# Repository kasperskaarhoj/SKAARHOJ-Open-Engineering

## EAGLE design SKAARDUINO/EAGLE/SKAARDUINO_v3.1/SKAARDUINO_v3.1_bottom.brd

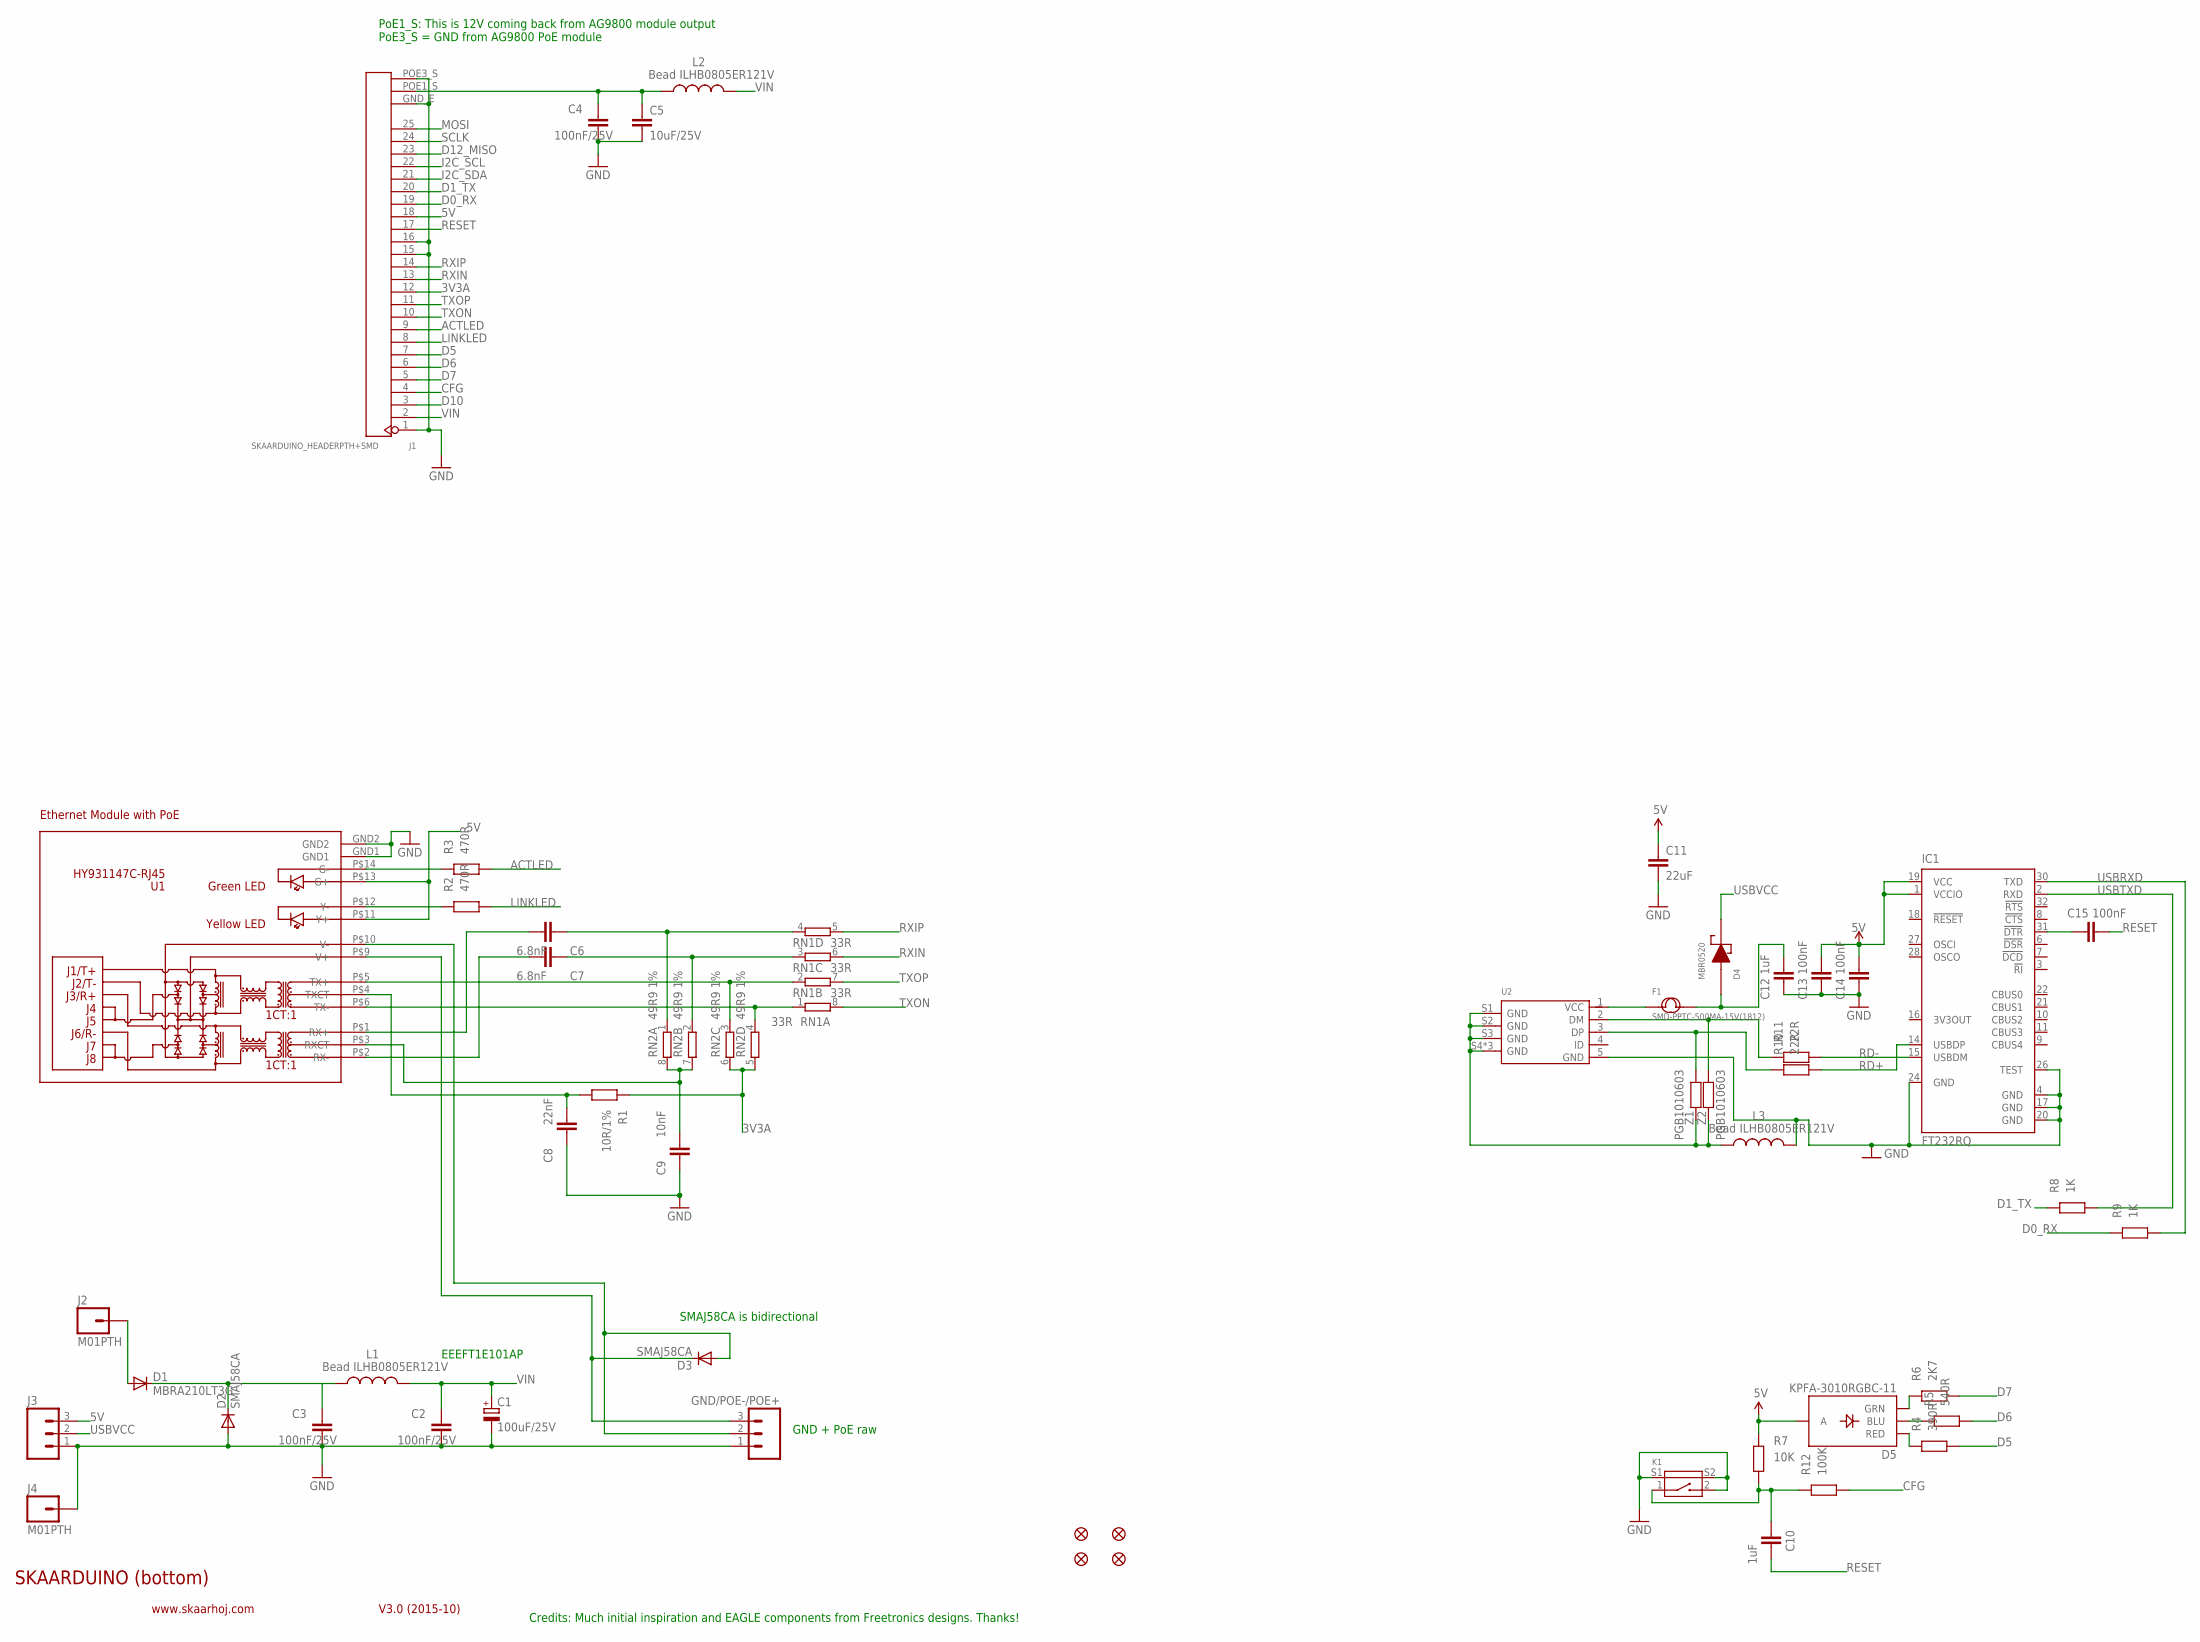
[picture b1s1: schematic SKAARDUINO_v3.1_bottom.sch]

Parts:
C1: 100uF/25V; PANASONIC_D
C2, C3, C4: 100nF/25V; C0402
C5: 10uF/25V; 0805
C6, C7: 6.8nF; 0402C
C8: 22nF; 0402C
C9: 10nF; 0402C
C10, C12: 1uF; 0402C
C11: 22uF; 0805
C13, C14, C15: 100nF; 0402C
D1: MBRA210LT3G; SMA-DIODE
D2, D3: SMAJ58CA; SMA-DIODE
D4: MBR0520; SOD-123
D5: KPFA-3010RGBC-11; LED-TRICOLOR-SMD
F1: SMD-PPTC-500MA-15V(1812); F1812
FID1, FID2, FID3, FID4: FIDUCIAL1X2.5; FIDUCIAL-1X2.5
GND/POE-/POE+: M03LOCK; 1X03_LOCK
IC1: FT232RQ; QFN32
J1: SKAARDUINO_HEADERPTH+SMD; SKAARDUINO_PTH_SMD_HEADER
J2, J4: M01PTH; 1X01
J3: M03LOCK; 1X03_LOCK
K1: SMD-BUTTON-2+2P; SW4-SMD-7.0X3.5X3.5MM-90D
L1, L2, L3: Bead ILHB0805ER121V; L2012C
R1: 10R/1%; 0402
R2, R3: 470R; 0402
R4: 390R; 0402
R5: 540R; 0402
R6: 2K7; 0402
R7: 10K; 0402
R8, R9: 1K; 0402
R10, R11: 22R; 0402
R12: 100K; 0402
RN1: 33R; CAY16
RN2: 49R9 1%; CAY16
U1: HY931147C-RJ45; HY931147C
U2: MICRO-USB-SMD-B-WITHOUT-POST-W/P(ST-USB-001G); MICRO-USB5+4P-SMD-0.65-B
Z1, Z2: PGB1010603; C0402

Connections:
3V3A: J1.12, R1.2, RN2.5 (2), RN2.6 (2)
5V: C11.1, C13.2, C14.2, D5.A, IC1.1 (VCCIO), IC1.19 (VCC), J1.18, J3.3, R7.2, U1.P$11 (Y+), U1.P$13 (G+)
ACTLED: J1.9, R3.1
CFG: J1.4, R12.1
CFGSW: C10.2, K1.1, R7.1, R12.2
D0_RX: J1.19, R9.2
D1_TX: J1.20, R8.2
D5: J1.7, R4.1
D6: J1.6, R5.1
D7: J1.5, R6.1
D10: J1.3
D12_MISO: J1.23
GND: C1.-, C2.2, C3.2, C4.2, C5.2, C8.1, C9.1, C11.2, C12.1, C13.1, C14.1, D2.A, GND/POE-/POE+.1, IC1.4 (GND), IC1.17 (GND), IC1.20 (GND), IC1.24 (GND), IC1.26 (TEST), J1.1, J1.15, J1.16, J1.GND_E (26), J1.POE3_S (28), J3.1, J4.1, K1.2, K1.S1, K1.S2, L3.2, U1.GND1, U1.GND2, U2.5 (GND)
I2C_SCL: J1.22
I2C_SDA: J1.21
LINKLED: J1.8, R2.1
MOSI: J1.25
unnamed: C8.2, R1.1, U1.P$4 (TXCT)
unnamed: C4.1, C5.1, J1.POE1_S (27), L2.1
unnamed: D3.C, GND/POE-/POE+.3, U1.P$9 (V+)
unnamed: C3.1, D1.C, D2.C, L1.1
unnamed: D3.A, GND/POE-/POE+.2, U1.P$10 (V-)
unnamed: C12.2, D4.2 (AN), F1.2
unnamed: F1.1, U2.1 (VCC)
unnamed: C7.2, U1.P$2 (RX-)
unnamed: D5.G (GRN), R6.2
unnamed: C6.2, U1.P$1 (RX+)
unnamed: D1.A, J2.1
unnamed: D5.B (BLU), R5.2
unnamed: D5.R (RED), R4.2
unnamed: R10.2, U2.3 (DP), Z1.1
unnamed: R11.2, U2.2 (DM), Z2.1
unnamed: C15.1, IC1.31 (!DTR)
unnamed: L3.1, U2.S1 (GND), U2.S2 (GND), U2.S3 (GND), U2.S4 (GND), U2.S5 (GND), U2.S6 (GND), Z1.2, Z2.2
unnamed: R3.2, U1.P$14 (G-)
unnamed: C9.2, RN2.7 (2), RN2.8 (2), U1.P$3 (RXCT)
unnamed: R2.2, U1.P$12 (Y-)
RD+: IC1.14 (USBDP), R10.1
RD-: IC1.15 (USBDM), R11.1
RESET: C10.1, C15.2, J1.17
RXIN: J1.13, RN1.6 (2)
RXIN_E: C7.1, RN1.3 (1), RN2.2 (1)
RXIP: J1.14, RN1.5 (2)
RXIP_E: C6.1, RN1.4 (1), RN2.1
SCLK: J1.24
TXON: J1.10, RN1.8 (2)
TXON_E: RN1.1, RN2.4 (1), U1.P$6 (TX-)
TXOP: J1.11, RN1.7 (2)
TXOP_E: RN1.2 (1), RN2.3 (1), U1.P$5 (TX+)
USBRXD: IC1.30 (TXD), R9.1
USBTXD: IC1.2 (RXD), R8.1
USBVCC: D4.1 (CA), J3.2
VIN: C1.+, C2.1, J1.2, L1.2, L2.2

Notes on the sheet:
SKAARDUINO (bottom)
V3.0 (2015-10)
www.skaarhoj.com
Ethernet Module with PoE
Credits: Much initial inspiration and EAGLE components from Freetronics designs. Thanks!
EEEFT1E101AP
PoE1_S: This is 12V coming back from AG9800 module output PoE3_S = GND from AG9800 PoE module
GND + PoE raw
SMAJ58CA is bidirectional

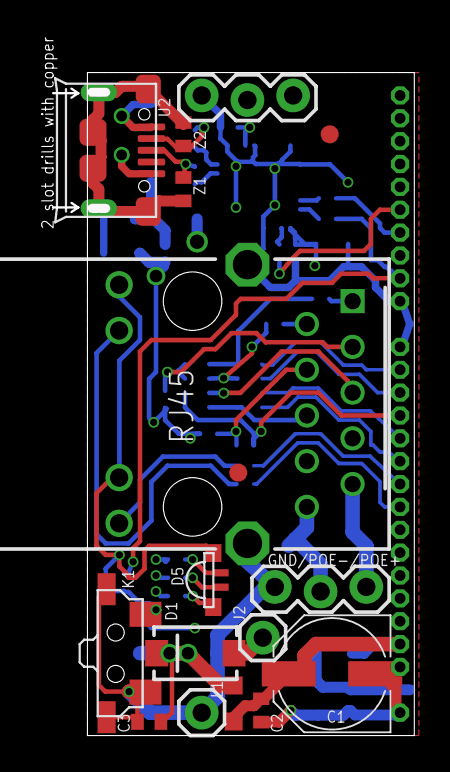
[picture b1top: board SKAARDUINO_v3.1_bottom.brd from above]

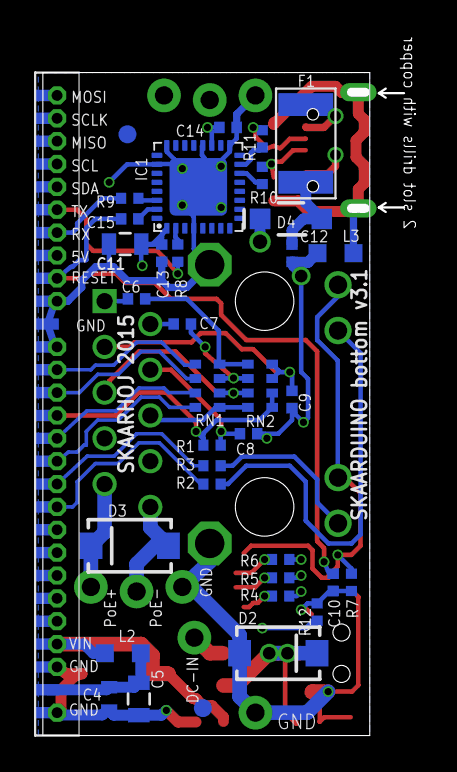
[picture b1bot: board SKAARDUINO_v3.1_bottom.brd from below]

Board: 4 copper layers, 20.1 x 36.8 mm, 53 parts (36 on the bottom side), 47 nets.

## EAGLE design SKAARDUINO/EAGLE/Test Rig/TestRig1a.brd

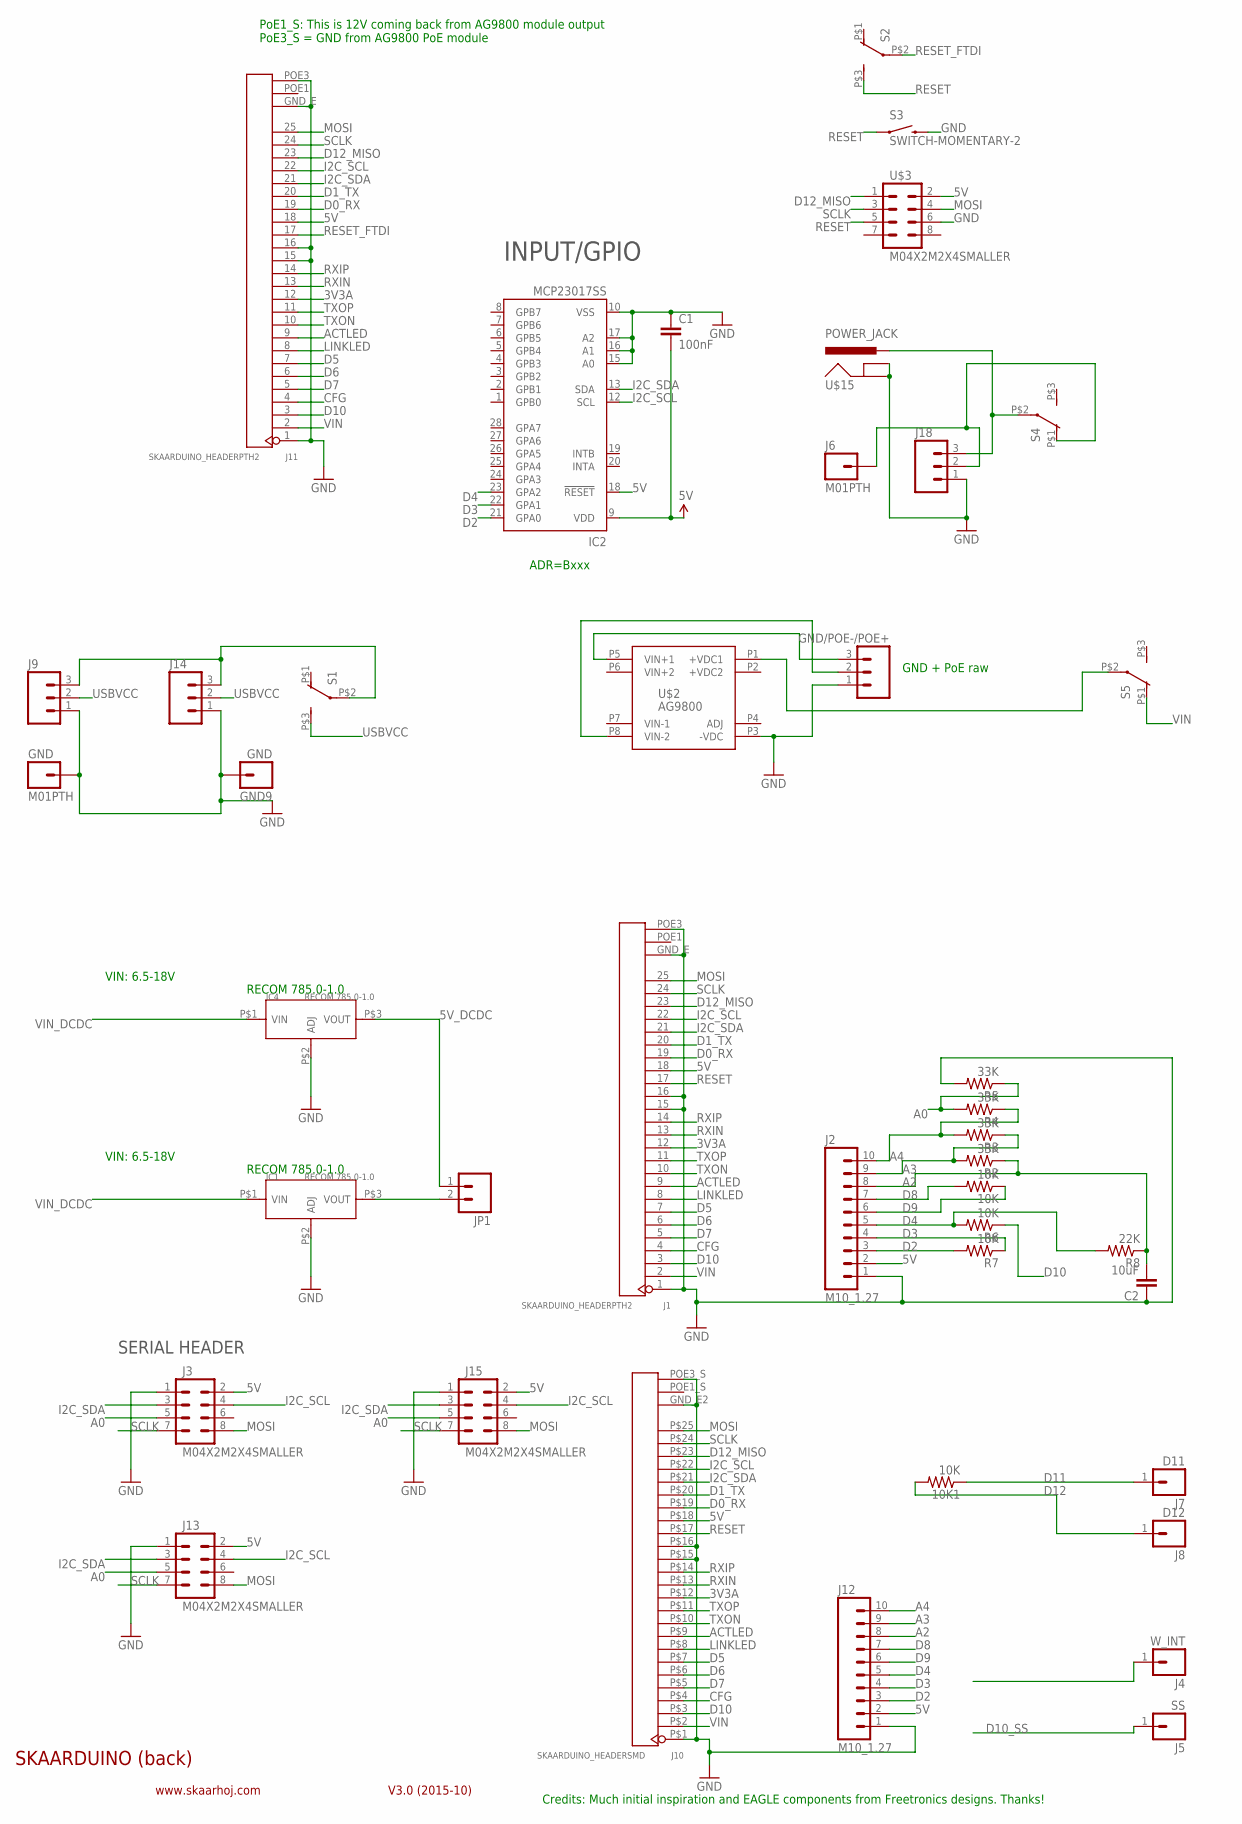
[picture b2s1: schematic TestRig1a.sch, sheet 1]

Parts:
10K, 10K1: 10K; 0603-RES
C1: 100nF; 0603-CAP
C2: 10uF; 0805
GND: M01PTH; 1X01
GND9: GND; 1X01
GND/POE-/POE+: M03LOCK; 1X03_LOCK
IC1, IC4: RECOM 785.0-1.0; RECOM_785.0-1.0
IC2: MCP23017SS; SSOP28; MPN MCP23017-E/SS
J1, J11: SKAARDUINO_HEADERPTH2; SKAARDUINO_PTH_HEADER2
J2, J12: M10_1.27; M10X1
J3, J13, J15: M04X2M2X4SMALLER; M2X4SMALLER
J4: W_INT; M1X1
J5: SS; M1X1
J6: M01PTH; 1X01
J7: D11; M1X1
J8: D12; M1X1
J9, J14, J18: M03LOCK; 1X03_LOCK
J10: SKAARDUINO_HEADERSMD; SKAARDUINO_SMD_HEADER
JP1: M02PTH; 1X02
R2, R3, R4, R5: 33K; 0603-RES
R6, R7: 10K; 0603-RES
R8: 22K; 0603-RES
S1, S2, S4, S5: SWITCH-DPST; TECONNECTIVITY-DPST
S3: SWITCH-MOMENTARY-2; TACTILE_SWITCH_TALL
U$2: AG9800
U$3: M04X2M2X4SMALLER; M2X4SMALLER
U$15: POWER_JACK; POWER_JACK_SMD

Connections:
3V3A: J1.12, J10.P$12 (12), J11.12
5V: C1.2, IC2.9 (VDD), IC2.18 (!RESET), J1.18, J2.2, J3.2, J10.P$18 (18), J11.18, J12.2, J13.2, J15.2, U$3.2
5V_DCDC: IC4.P$3 (VOUT), JP1.1
A0: J3.5, J13.5, J15.5, R4.2, R5.1
A2: C2.2, J2.8, J12.8, R2.1, R8.1
A3: J2.9, J12.9, R2.2, R3.1
A4: J2.10, J12.10, R3.2, R4.1
ACTLED: J1.9, J10.P$9 (9), J11.9
CFG: J1.4, J10.P$4 (4), J11.4
D0_RX: J1.19, J10.P$19 (19), J11.19
D1_TX: J1.20, J10.P$20 (20), J11.20
D2: IC2.21 (GPA0), J2.3, J12.3, R7.2
D3: IC2.22 (GPA1), J2.4, J12.4, R7.1
D4: IC2.23 (GPA2), J2.5, J12.5, R6.2, R8.2
D5: J1.7, J10.P$7 (7), J11.7
D6: J1.6, J10.P$6 (6), J11.6
D7: J1.5, J10.P$5 (5), J11.5
D8: 10K.2, J2.7, J12.7
D9: 10K.1, J2.6, J12.6
D10: J1.3, J10.P$3 (3), J11.3, R6.1
D10_SS: J5.1
D11: 10K1.1, J7.1
D12: 10K1.2, J8.1
D12_MISO: J1.23, J10.P$23 (23), J11.23, U$3.1
GND: C1.1, C2.1, GND.1, GND9.1, GND/POE-/POE+.1, IC1.P$2 (ADJ), IC2.10 (VSS), IC2.15 (A0), IC2.16 (A1), IC2.17 (A2), IC4.P$2 (ADJ), J1.1, J1.15, J1.16, J1.GND_E (26), J1.POE3 (28), J2.1, J3.1, J9.1, J10.GND_E2 (26), J10.P$1 (1), J10.P$15 (15), J10.P$16 (16), J10.POE3_S (28), J11.1, J11.15, J11.16, J11.GND_E (26), J11.POE3 (28), J12.1, J13.1, J14.1, J15.1, J18.1, R5.2, S3.B2 (2), U$2.P3 (-VDC), U$3.6, U$15.GND, U$15.SHUNT (GNDBREAK)
I2C_SCL: IC2.12 (SCL), J1.22, J3.4, J10.P$22 (22), J11.22, J13.4, J15.4
I2C_SDA: IC2.13 (SDA), J1.21, J3.3, J10.P$21 (21), J11.21, J13.3, J15.3
LINKLED: J1.8, J10.P$8 (8), J11.8
MOSI: J1.25, J3.8, J10.P$25 (25), J11.25, J13.8, J15.8, U$3.4
unnamed: J18.3, S4.P$2, U$15.PWR
unnamed: S5.P$2, U$2.P1 (+VDC1)
unnamed: IC1.P$3 (VOUT), JP1.2
unnamed: GND/POE-/POE+.2, U$2.P8 (VIN-2)
unnamed: GND/POE-/POE+.3, U$2.P5 (VIN+1)
unnamed: J9.3, J14.3, S1.P$2
unnamed: J6.1, J18.2, S4.P$1 (O)
RESET: J1.17, J10.P$17 (17), S2.P$3 (S), S3.A2 (1), U$3.5
RESET_FTDI: J11.17, S2.P$2
RXIN: J1.13, J10.P$13 (13), J11.13
RXIP: J1.14, J10.P$14 (14), J11.14
SCLK: J1.24, J3.7, J10.P$24 (24), J11.24, J13.7, J15.7, U$3.3
TXON: J1.10, J10.P$10 (10), J11.10
TXOP: J1.11, J10.P$11 (11), J11.11
USBVCC: J9.2, J14.2, S1.P$3 (S)
VIN: J1.2, J10.P$2 (2), J11.2, S5.P$1 (O)
VIN+2: U$2.P6 (VIN+2)
VIN-1: U$2.P7 (VIN-1)
VIN_DCDC: IC1.P$1 (VIN), IC4.P$1 (VIN)

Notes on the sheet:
SKAARDUINO (back)
V3.0 (2015-10)
www.skaarhoj.com
SERIAL HEADER
Credits: Much initial inspiration and EAGLE components from Freetronics designs. Thanks!
RECOM 785.0-1.0
VIN: 6.5-18V
PoE1_S: This is 12V coming back from AG9800 module output PoE3_S = GND from AG9800 PoE module
GND + PoE raw
ADR=Bxxx
INPUT/GPIO

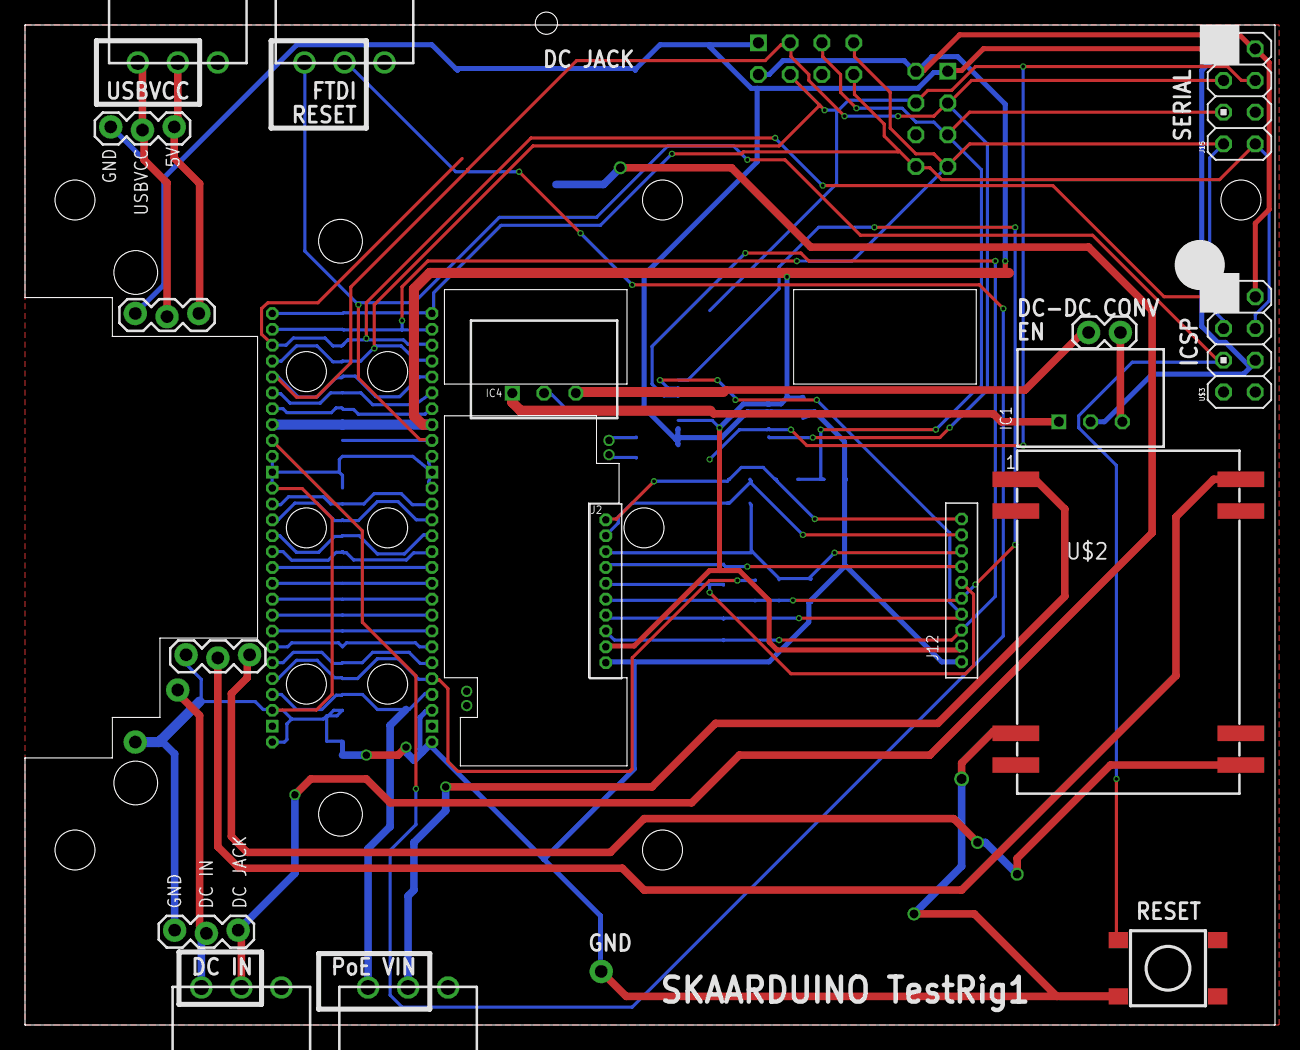
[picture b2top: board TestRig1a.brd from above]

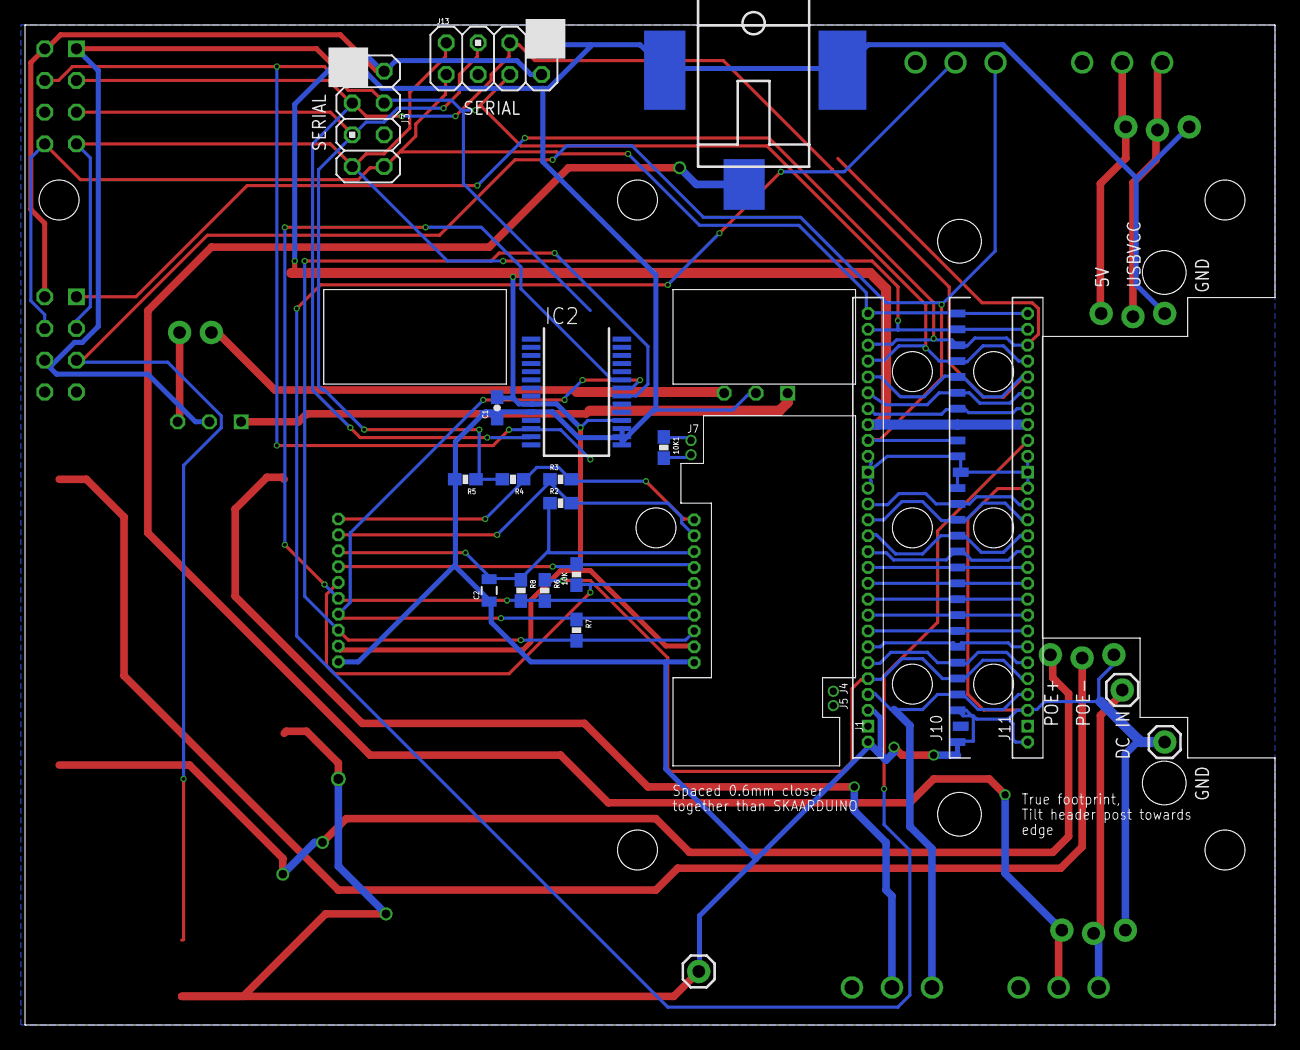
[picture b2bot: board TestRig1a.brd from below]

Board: 4 copper layers, 100.0 x 80.0 mm, 42 parts (22 on the bottom side), 45 nets.

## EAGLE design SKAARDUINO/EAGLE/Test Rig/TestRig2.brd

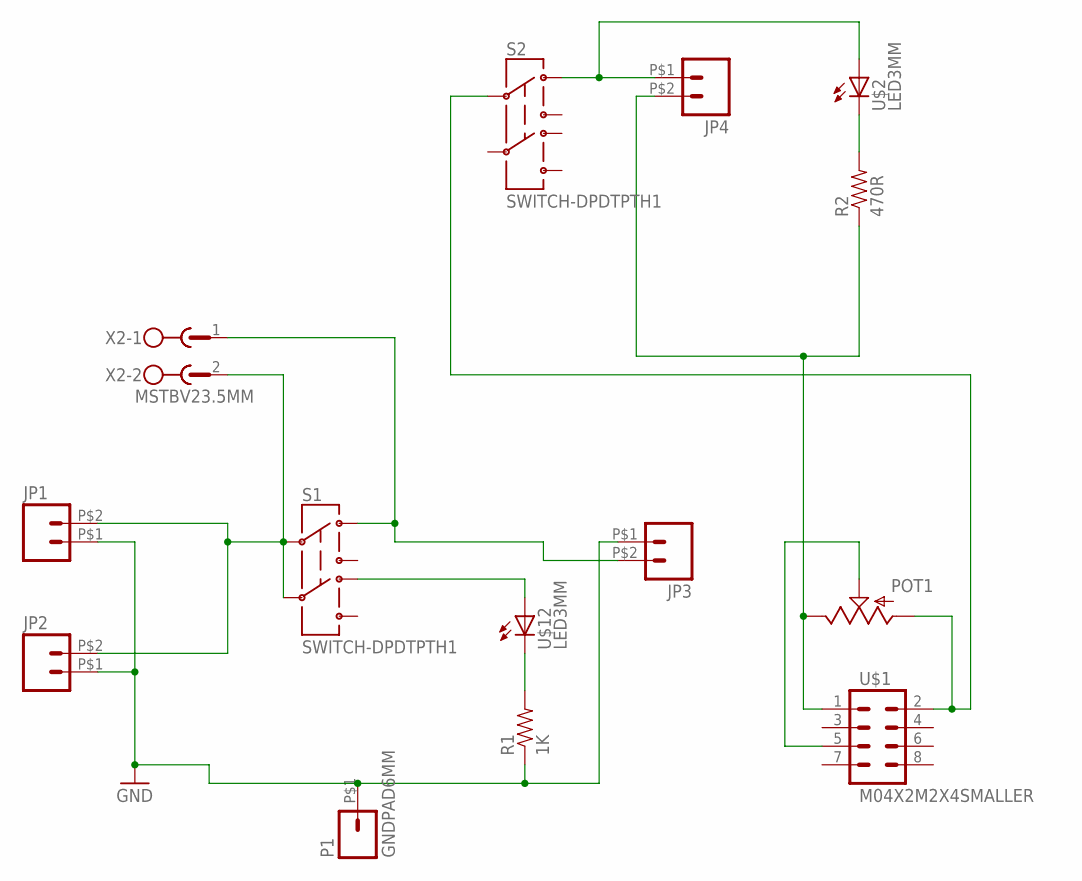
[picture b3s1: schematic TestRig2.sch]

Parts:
JP1, JP2, JP3, JP4: M02PTH2; 1X02_BIG
P1: GNDPAD6MM; 3.2MMPAD6MM
POT1: POT; ALPS_POT
R1: 1K; 0603-RES
R2: 470R; 0603-RES
S1, S2: SWITCH-DPDTPTH1; TECONNECTIVITY-DPDT
U$1: M04X2M2X4SMALLER; M2X4SMALLER
U$2, U$12: LED3MM
X2: MSTBV23.5MM; MSTBV2-3.5

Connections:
GND: JP1.P$1 (1), JP2.P$1 (1), JP3.P$1 (1), P1.P$1, R1.1
unnamed: JP3.P$2 (2), S1.P$1 (1), X2.1
unnamed: JP1.P$2 (2), JP2.P$2 (2), S1.P$2 (2), S1.P$5 (5), X2.2
unnamed: R2.2, U$2.K (C)
unnamed: S1.P$4 (4), U$12.A
unnamed: R1.2, U$12.K (C)
unnamed: JP4.P$2 (2), POT1.P$1 (E), R2.1, U$1.1
unnamed: POT1.P$3 (A), S2.P$2 (2), U$1.2
unnamed: POT1.P$2 (S), U$1.5
unnamed: JP4.P$1 (1), S2.P$1 (1), U$2.A

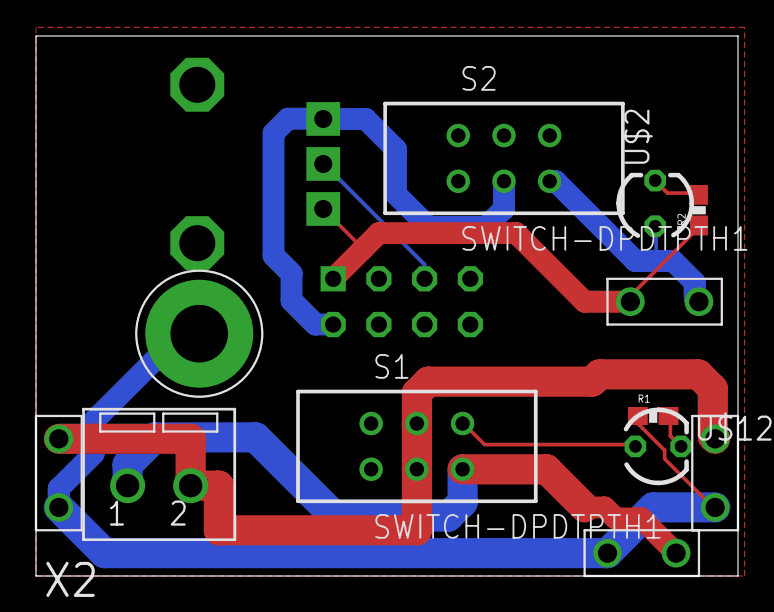
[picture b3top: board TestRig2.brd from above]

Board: 2 copper layers, 39.0 x 30.0 mm, 14 parts (1 on the bottom side), 10 nets.

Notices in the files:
parts and their libraries:
SparkFun: Licensing: CC v3.0 Share-Alike You are welcome to use this library for commercial purposes.
